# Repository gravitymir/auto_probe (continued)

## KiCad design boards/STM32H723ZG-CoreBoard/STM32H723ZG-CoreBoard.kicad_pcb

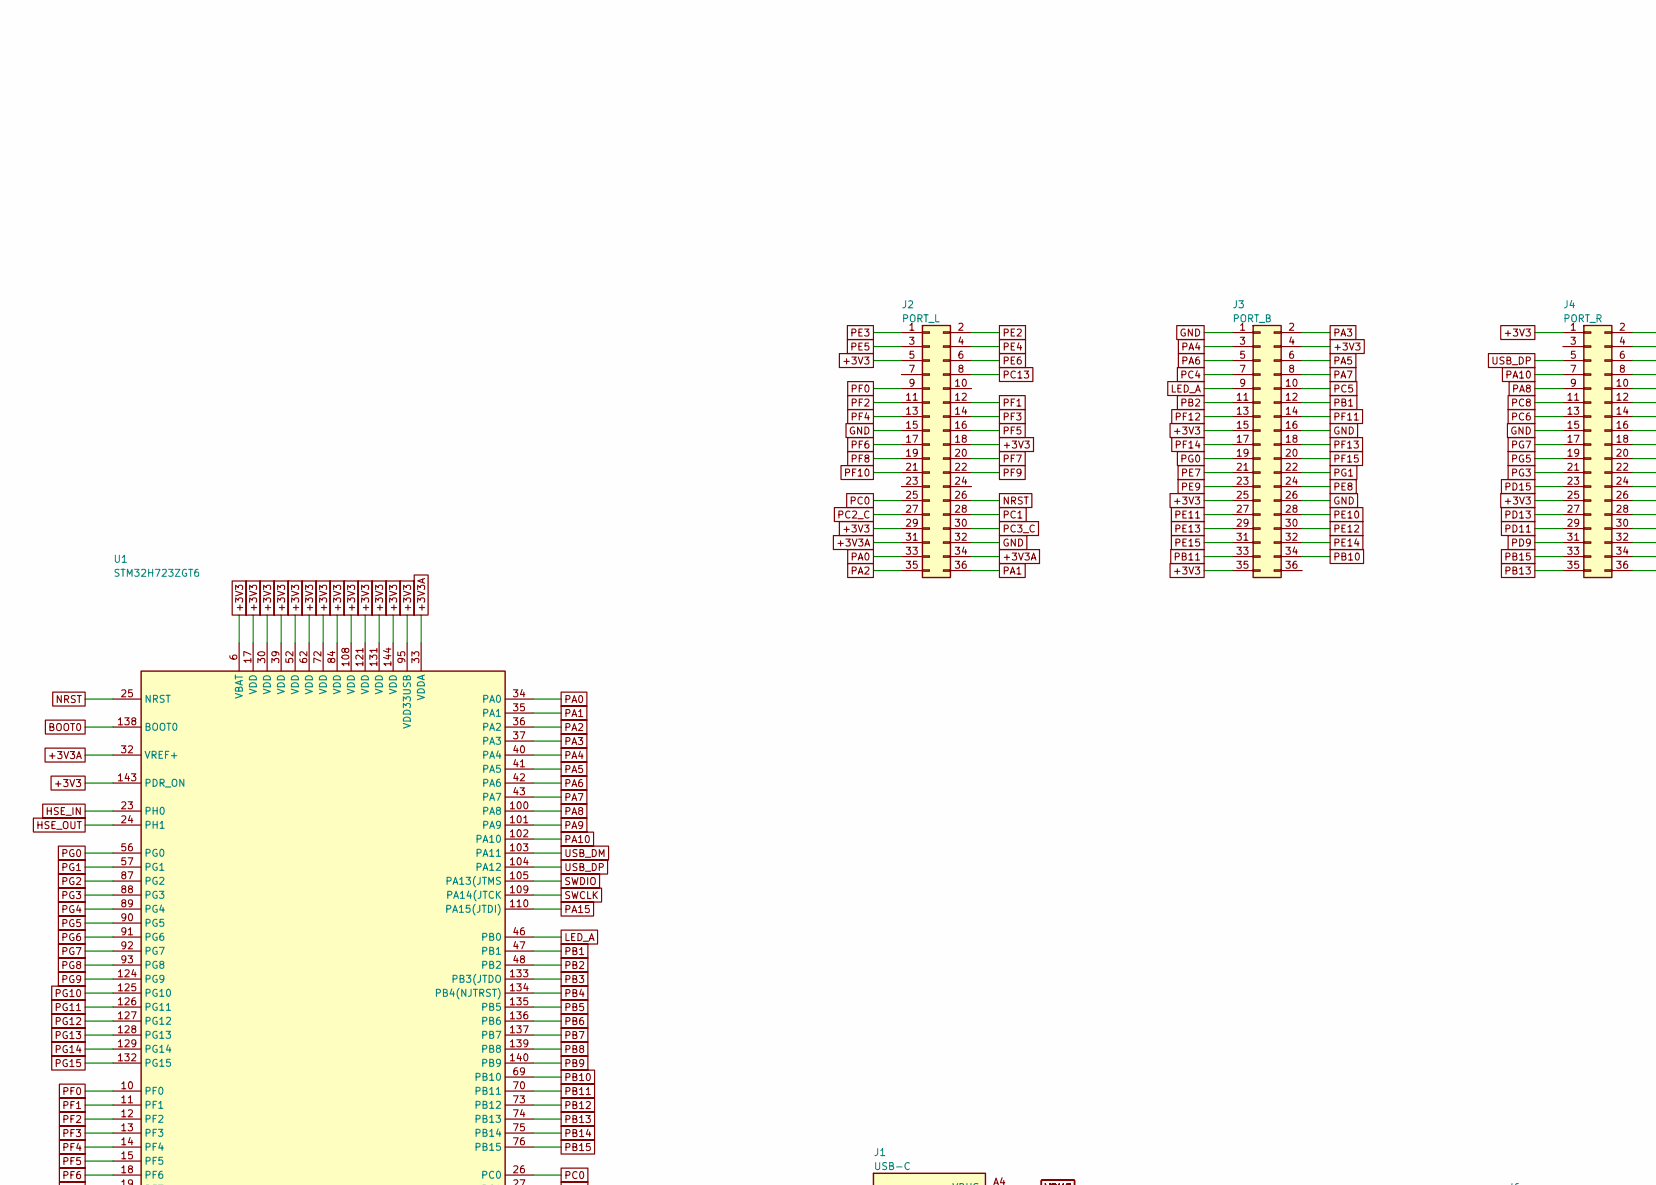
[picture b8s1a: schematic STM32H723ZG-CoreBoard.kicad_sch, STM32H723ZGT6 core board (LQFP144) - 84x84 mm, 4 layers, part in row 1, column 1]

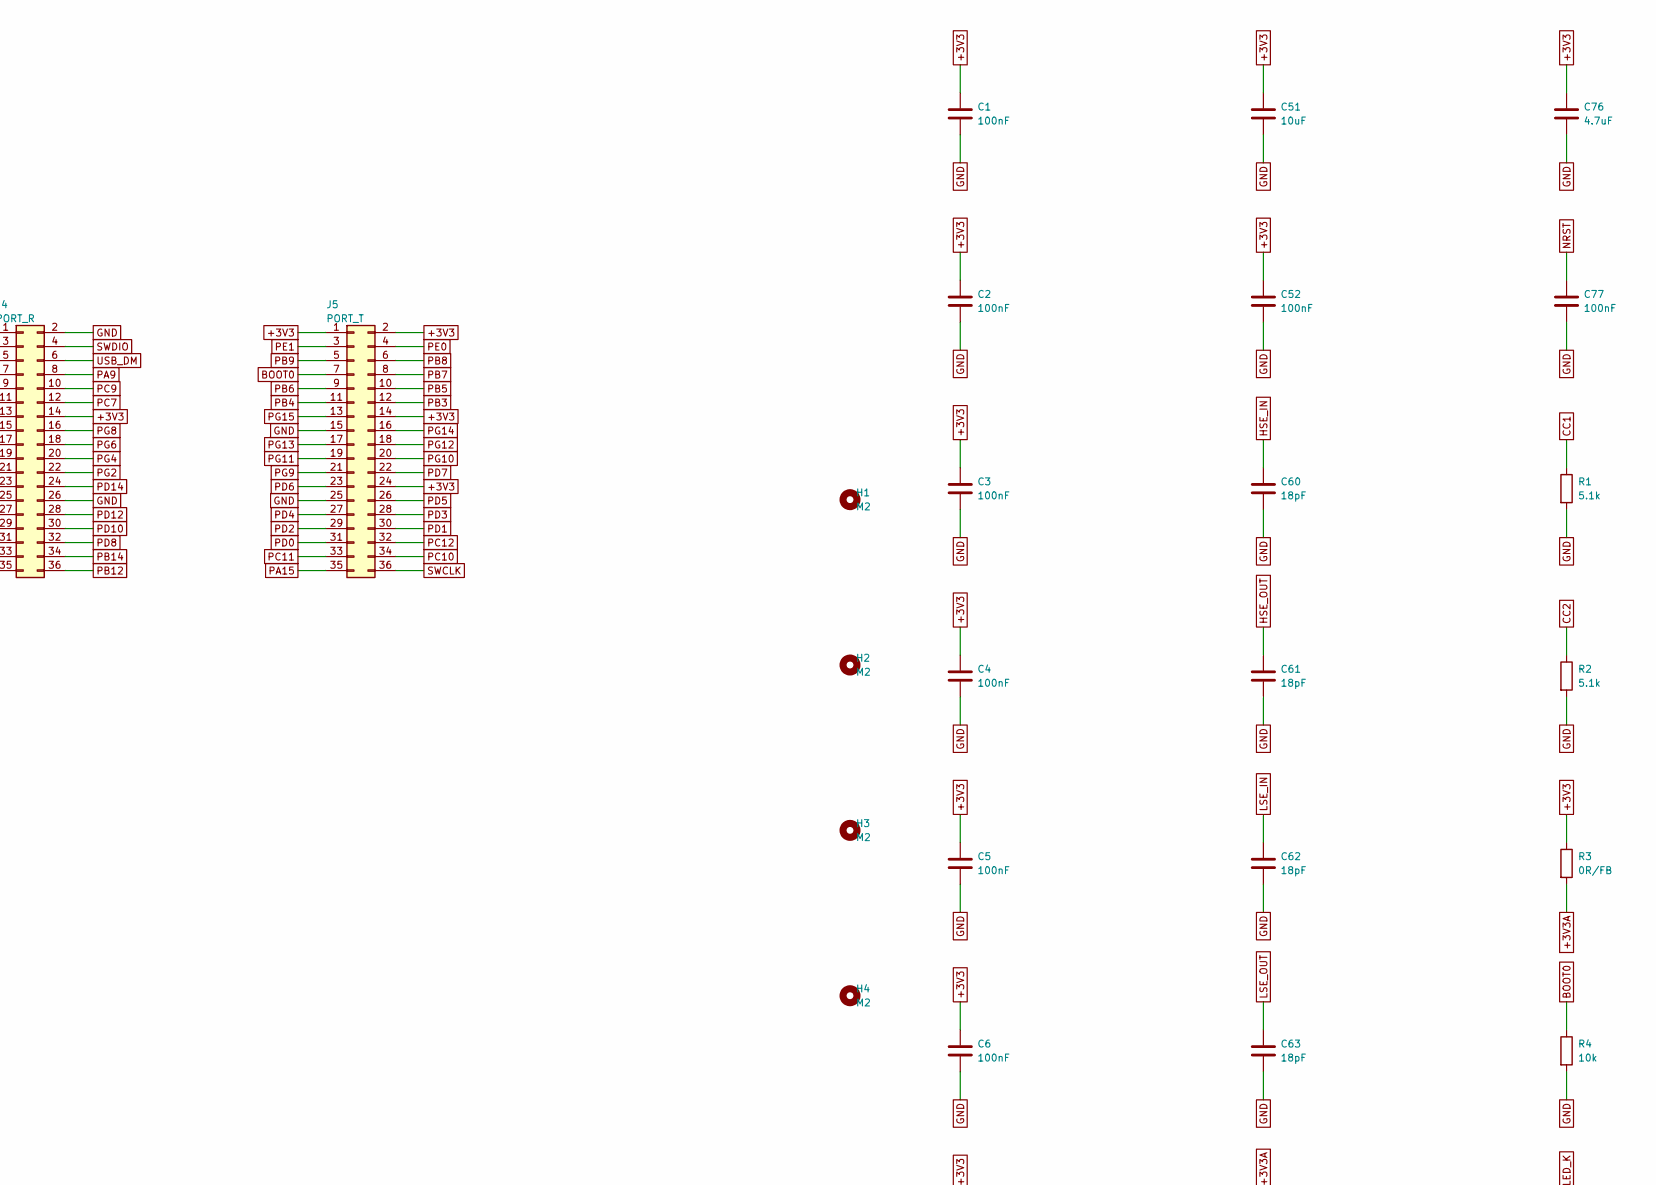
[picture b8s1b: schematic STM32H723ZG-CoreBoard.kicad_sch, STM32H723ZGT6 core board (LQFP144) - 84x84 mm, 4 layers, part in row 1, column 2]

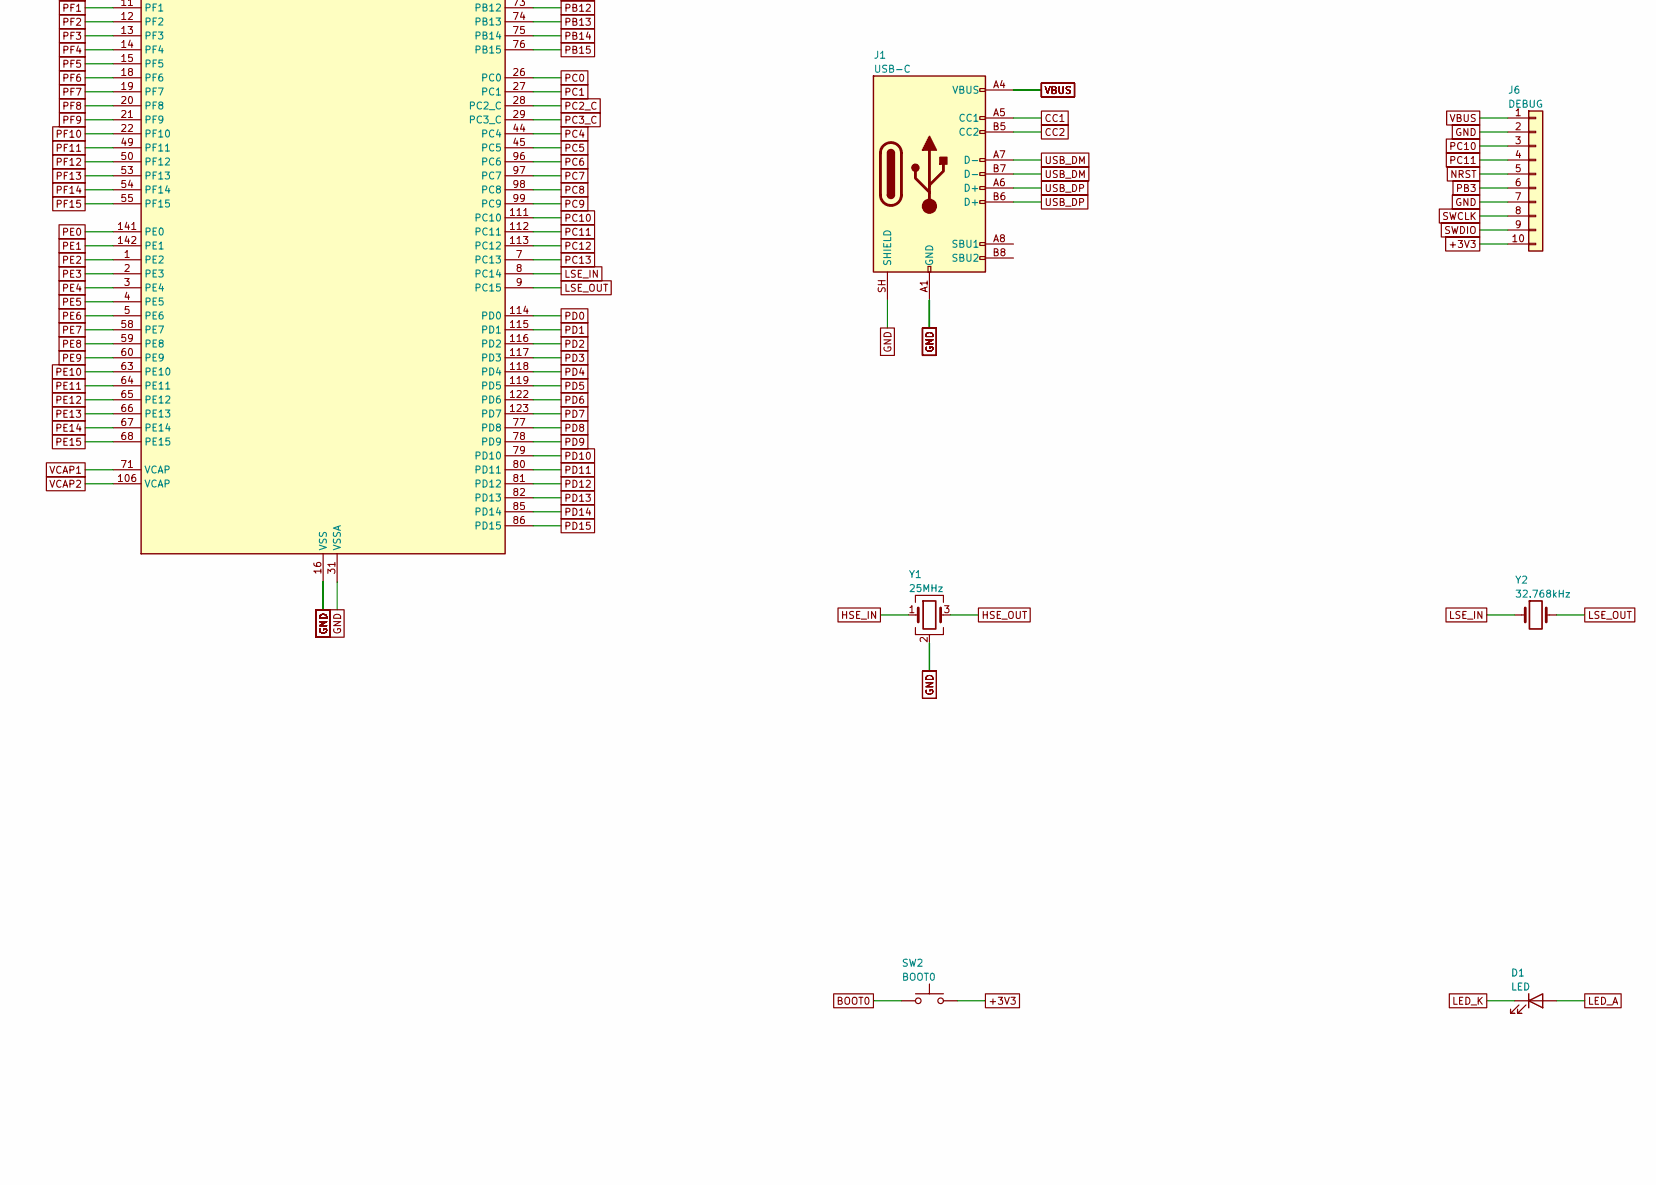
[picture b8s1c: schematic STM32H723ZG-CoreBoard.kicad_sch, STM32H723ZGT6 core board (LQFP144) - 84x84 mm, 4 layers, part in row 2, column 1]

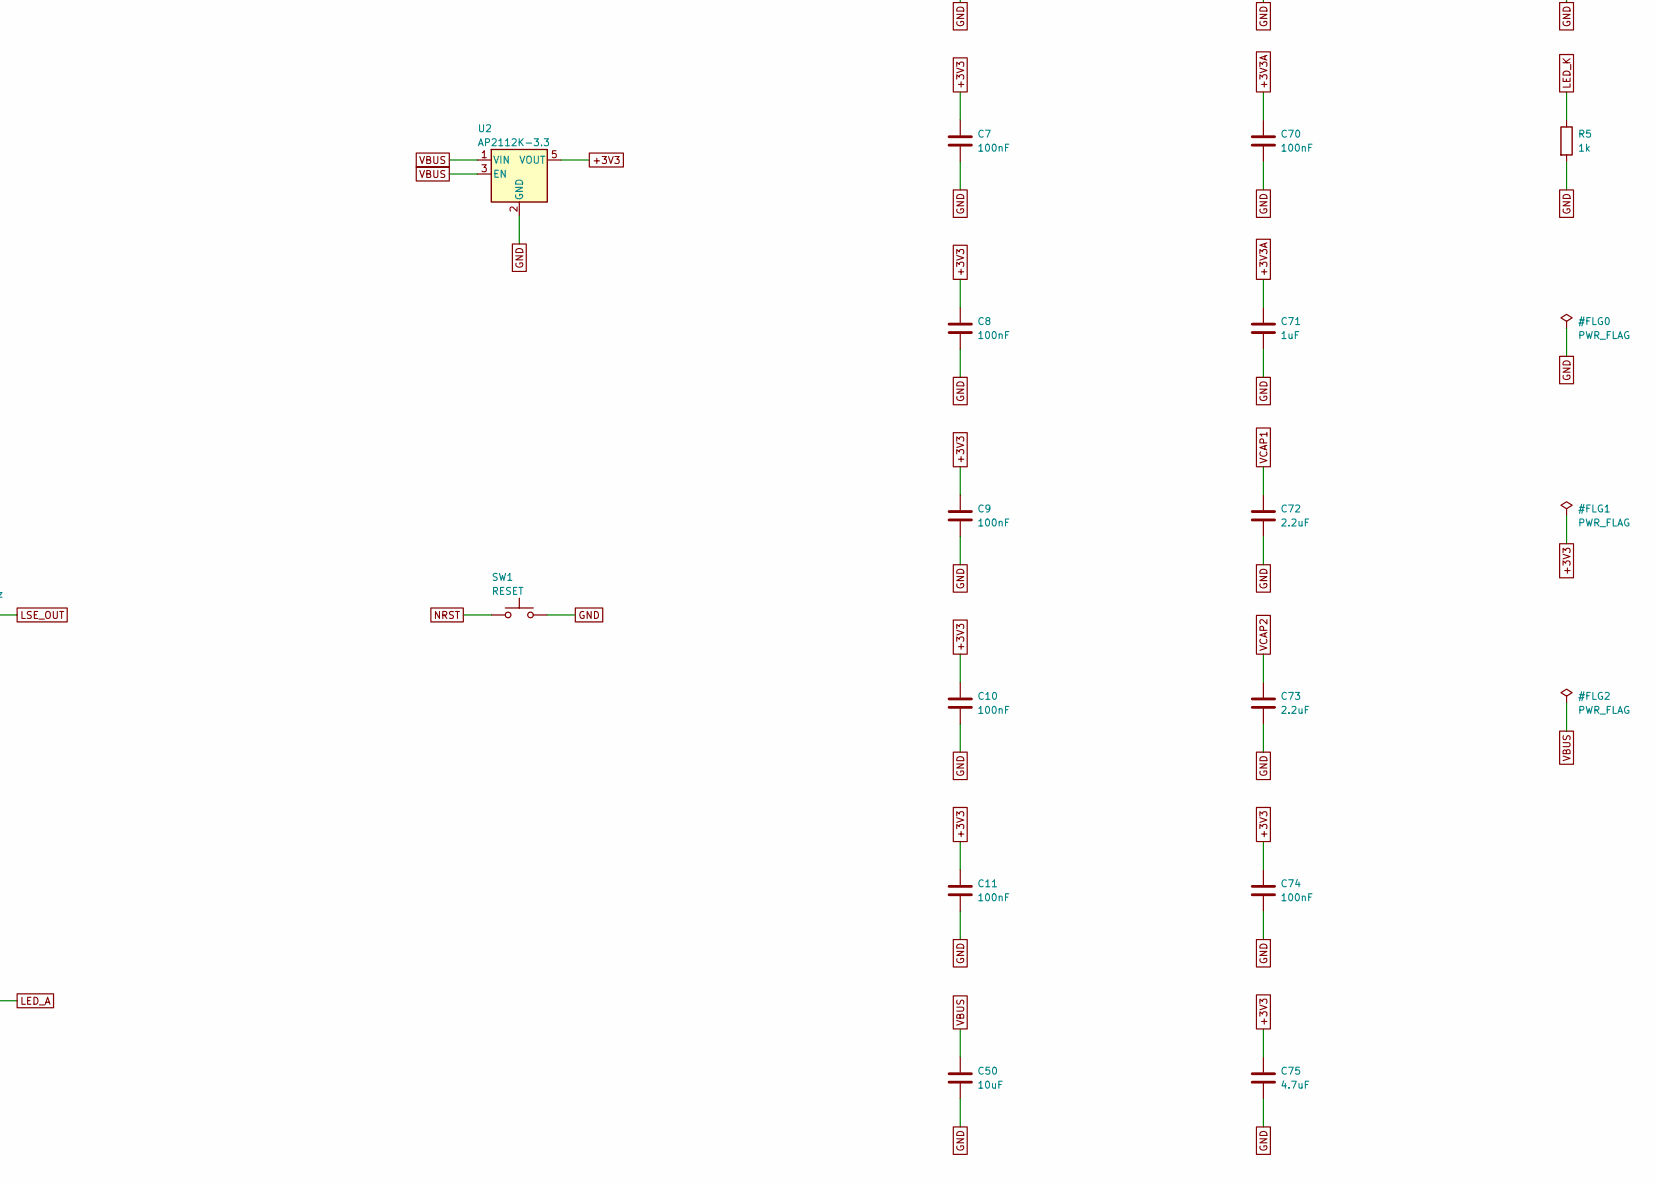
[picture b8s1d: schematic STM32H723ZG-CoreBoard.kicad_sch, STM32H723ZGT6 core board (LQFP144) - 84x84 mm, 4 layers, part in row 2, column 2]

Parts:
C1, C2, C3, C4, C5, C6, C7, C8, C9, C10, C11, C70, C74, C77: 100nF; C_0402_1005Metric
C50, C51: 10uF; C_0805_2012Metric
C52: 100nF; C_0603_1608Metric
C60, C61, C62, C63: 18pF; C_0402_1005Metric
C71: 1uF; C_0603_1608Metric
C72, C73: 2.2uF; C_0603_1608Metric
C75, C76: 4.7uF; C_0805_2012Metric
D1: LED; LED_0805_2012Metric
H1, H2, H3, H4: M2; MountingHole_2.2mm_M2
J1: USB-C; USB_C_Receptacle_HRO_TYPE-C-31-M-12
J2: PORT_L; PinHeader_2x18_P2.54mm_Vertical
J3: PORT_B; PinHeader_2x18_P2.54mm_Vertical
J4: PORT_R; PinHeader_2x18_P2.54mm_Vertical
J5: PORT_T; PinHeader_2x18_P2.54mm_Vertical
J6: DEBUG; PinHeader_1x10_P2.54mm_Vertical
R1, R2: 5.1k; R_0402_1005Metric
R3: 0R/FB; R_0402_1005Metric
R4: 10k; R_0402_1005Metric
R5: 1k; R_0402_1005Metric
SW1: RESET; SW_SPST_SKQG_WithoutStem
SW2: BOOT0; SW_SPST_SKQG_WithoutStem
U1: STM32H723ZGT6; LQFP-144_20x20mm_P0.5mm
U2: AP2112K-3.3; SOT-23-5
Y1: 25MHz; Crystal_SMD_3225-4Pin_3.2x2.5mm
Y2: 32.768kHz; Crystal_SMD_MicroCrystal_CC7V-T1A-2Pin_3.2x1.5mm

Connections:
+3V3: C1.1, C2.1, C3.1, C4.1, C5.1, C6.1, C7.1, C8.1, C9.1, C10.1, C11.1, C51.1, C52.1, C74.1, C75.1, C76.1, J2.5, J2.18, J2.29, J3.4, J3.15, J3.25, J3.35, J4.1, J4.14, J4.25, J5.1, J5.2, J5.14, J5.24, J6.10, R3.1, SW2.2, U1.6 (VBAT), U1.17 (VDD), U1.30 (VDD), U1.39 (VDD), U1.52 (VDD), U1.62 (VDD), U1.72 (VDD), U1.84 (VDD), U1.95 (VDD33USB), U1.108 (VDD), U1.121 (VDD), U1.131 (VDD), U1.143 (PDR_ON), U1.144 (VDD), U2.5 (VOUT)
+3V3A: C70.1, C71.1, J2.31, J2.34, R3.2, U1.32 (VREF+), U1.33 (VDDA)
BOOT0: J5.7, R4.1, SW2.1, U1.138 (BOOT0)
CC1: J1.A5 (CC1), R1.1
CC2: J1.B5 (CC2), R2.1
GND: C1.2, C2.2, C3.2, C4.2, C5.2, C6.2, C7.2, C8.2, C9.2, C10.2, C11.2, C50.2, C51.2, C52.2, C60.2, C61.2, C62.2, C63.2, C70.2, C71.2, C72.2, C73.2, C74.2, C75.2, C76.2, C77.2, J1.A1 (GND), J1.A12 (GND), J1.B1 (GND), J1.B12 (GND), J1.SH (SHIELD), J2.15, J2.32, J3.1, J3.16, J3.26, J4.2, J4.15, J4.26, J5.15, J5.25, J6.2, J6.7, R1.2, R2.2, R4.2, R5.2, SW1.2, U1.16 (VSS), U1.31 (VSSA), U1.38 (VSS), U1.51 (VSS), U1.61 (VSS), U1.83 (VSS), U1.94 (VSS), U1.107 (VSS), U1.120 (VSS), U1.130 (VSS), U2.2 (GND), Y1.2 (G), Y1.4 (G)
HSE_IN: C60.1, U1.23 (PH0), Y1.1
HSE_OUT: C61.1, U1.24 (PH1), Y1.3
LED_A: D1.2 (A), J3.9, U1.46 (PB0)
LED_K: D1.1 (K), R5.1
LSE_IN: C62.1, U1.8 (PC14), Y2.1
LSE_OUT: C63.1, U1.9 (PC15), Y2.2
NRST: C77.1, J2.26, J6.5, SW1.1, U1.25 (NRST)
PA0: J2.33, U1.34 (PA0)
PA1: J2.36, U1.35 (PA1)
PA2: J2.35, U1.36 (PA2)
PA3: J3.2, U1.37 (PA3)
PA4: J3.3, U1.40 (PA4)
PA5: J3.6, U1.41 (PA5)
PA6: J3.5, U1.42 (PA6)
PA7: J3.8, U1.43 (PA7)
PA8: J4.9, U1.100 (PA8)
PA9: J4.8, U1.101 (PA9)
PA10: J4.7, U1.102 (PA10)
PA15: J5.35, U1.110 (PA15(JTDI))
PB1: J3.12, U1.47 (PB1)
PB2: J3.11, U1.48 (PB2)
PB3: J5.12, J6.6, U1.133 (PB3(JTDO)
PB4: J5.11, U1.134 (PB4(NJTRST))
PB5: J5.10, U1.135 (PB5)
PB6: J5.9, U1.136 (PB6)
PB7: J5.8, U1.137 (PB7)
PB8: J5.6, U1.139 (PB8)
PB9: J5.5, U1.140 (PB9)
PB10: J3.34, U1.69 (PB10)
PB11: J3.33, U1.70 (PB11)
PB12: J4.36, U1.73 (PB12)
PB13: J4.35, U1.74 (PB13)
PB14: J4.34, U1.75 (PB14)
PB15: J4.33, U1.76 (PB15)
PC0: J2.25, U1.26 (PC0)
PC1: J2.28, U1.27 (PC1)
PC2_C: J2.27, U1.28 (PC2_C)
PC3_C: J2.30, U1.29 (PC3_C)
PC4: J3.7, U1.44 (PC4)
PC5: J3.10, U1.45 (PC5)
PC6: J4.13, U1.96 (PC6)
PC7: J4.12, U1.97 (PC7)
PC8: J4.11, U1.98 (PC8)
PC9: J4.10, U1.99 (PC9)
PC10: J5.34, J6.3, U1.111 (PC10)
PC11: J5.33, J6.4, U1.112 (PC11)
PC12: J5.32, U1.113 (PC12)
PC13: J2.8, U1.7 (PC13)
PD0: J5.31, U1.114 (PD0)
PD1: J5.30, U1.115 (PD1)
PD2: J5.29, U1.116 (PD2)
PD3: J5.28, U1.117 (PD3)
PD4: J5.27, U1.118 (PD4)
PD5: J5.26, U1.119 (PD5)
PD6: J5.23, U1.122 (PD6)
PD7: J5.22, U1.123 (PD7)
PD8: J4.32, U1.77 (PD8)
PD9: J4.31, U1.78 (PD9)
PD10: J4.30, U1.79 (PD10)
PD11: J4.29, U1.80 (PD11)
PD12: J4.28, U1.81 (PD12)
PD13: J4.27, U1.82 (PD13)
PD14: J4.24, U1.85 (PD14)
PD15: J4.23, U1.86 (PD15)
PE0: J5.4, U1.141 (PE0)
PE1: J5.3, U1.142 (PE1)
PE2: J2.2, U1.1 (PE2)
PE3: J2.1, U1.2 (PE3)
PE4: J2.4, U1.3 (PE4)
PE5: J2.3, U1.4 (PE5)
PE6: J2.6, U1.5 (PE6)
PE7: J3.21, U1.58 (PE7)
PE8: J3.24, U1.59 (PE8)
PE9: J3.23, U1.60 (PE9)
PE10: J3.28, U1.63 (PE10)
PE11: J3.27, U1.64 (PE11)
PE12: J3.30, U1.65 (PE12)
PE13: J3.29, U1.66 (PE13)
PE14: J3.32, U1.67 (PE14)
PE15: J3.31, U1.68 (PE15)
PF0: J2.9, U1.10 (PF0)
PF1: J2.12, U1.11 (PF1)
PF2: J2.11, U1.12 (PF2)
PF3: J2.14, U1.13 (PF3)
PF4: J2.13, U1.14 (PF4)
PF5: J2.16, U1.15 (PF5)
PF6: J2.17, U1.18 (PF6)
PF7: J2.20, U1.19 (PF7)
PF8: J2.19, U1.20 (PF8)
PF9: J2.22, U1.21 (PF9)
PF10: J2.21, U1.22 (PF10)
PF11: J3.14, U1.49 (PF11)
PF12: J3.13, U1.50 (PF12)
PF13: J3.18, U1.53 (PF13)
PF14: J3.17, U1.54 (PF14)
PF15: J3.20, U1.55 (PF15)
PG0: J3.19, U1.56 (PG0)
PG1: J3.22, U1.57 (PG1)
PG2: J4.22, U1.87 (PG2)
PG3: J4.21, U1.88 (PG3)
PG4: J4.20, U1.89 (PG4)
PG5: J4.19, U1.90 (PG5)
PG6: J4.18, U1.91 (PG6)
PG7: J4.17, U1.92 (PG7)
PG8: J4.16, U1.93 (PG8)
PG9: J5.21, U1.124 (PG9)
PG10: J5.20, U1.125 (PG10)
PG11: J5.19, U1.126 (PG11)
PG12: J5.18, U1.127 (PG12)
PG13: J5.17, U1.128 (PG13)
PG14: J5.16, U1.129 (PG14)
PG15: J5.13, U1.132 (PG15)
SWCLK: J5.36, J6.8, U1.109 (PA14(JTCK)
SWDIO: J4.4, J6.9, U1.105 (PA13(JTMS)
USB_DM: J1.A7 (D-), J1.B7 (D-), J4.6, U1.103 (PA11)
USB_DP: J1.A6 (D+), J1.B6 (D+), J4.5, U1.104 (PA12)
VBUS: C50.1, J1.A4 (VBUS), J1.A9 (VBUS), J1.B4 (VBUS), J1.B9 (VBUS), J6.1, U2.1 (VIN), U2.3 (EN)
VCAP1: C72.1, U1.71 (VCAP)
VCAP2: C73.1, U1.106 (VCAP)

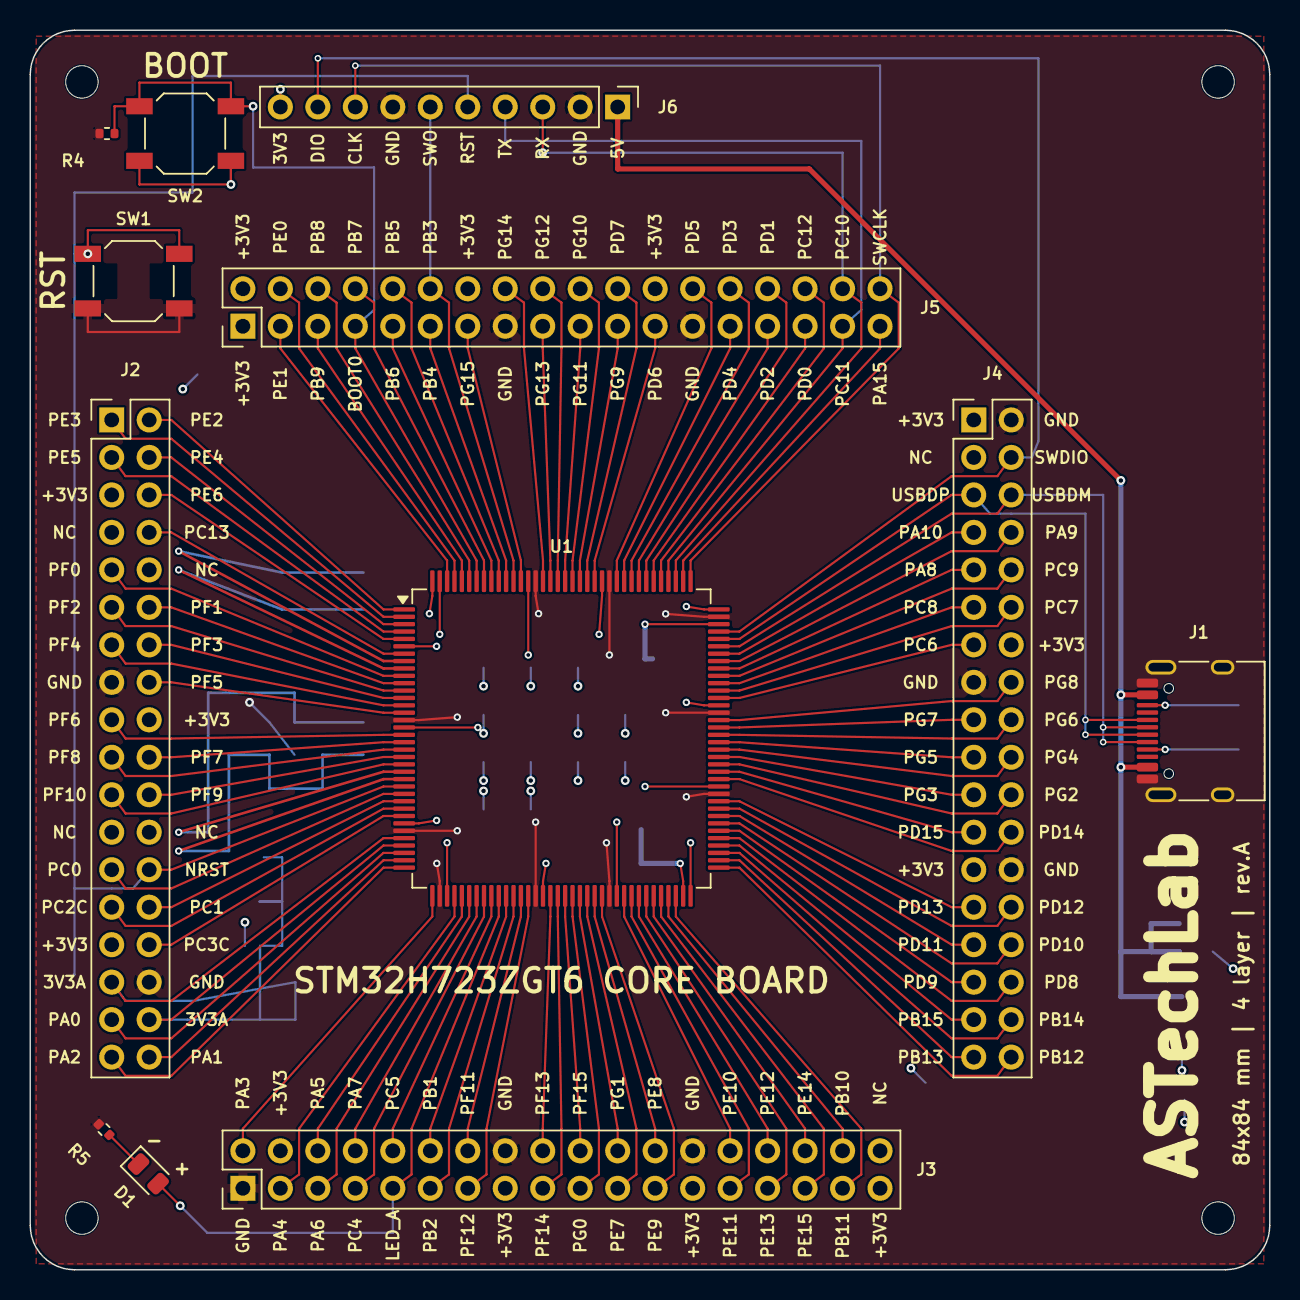
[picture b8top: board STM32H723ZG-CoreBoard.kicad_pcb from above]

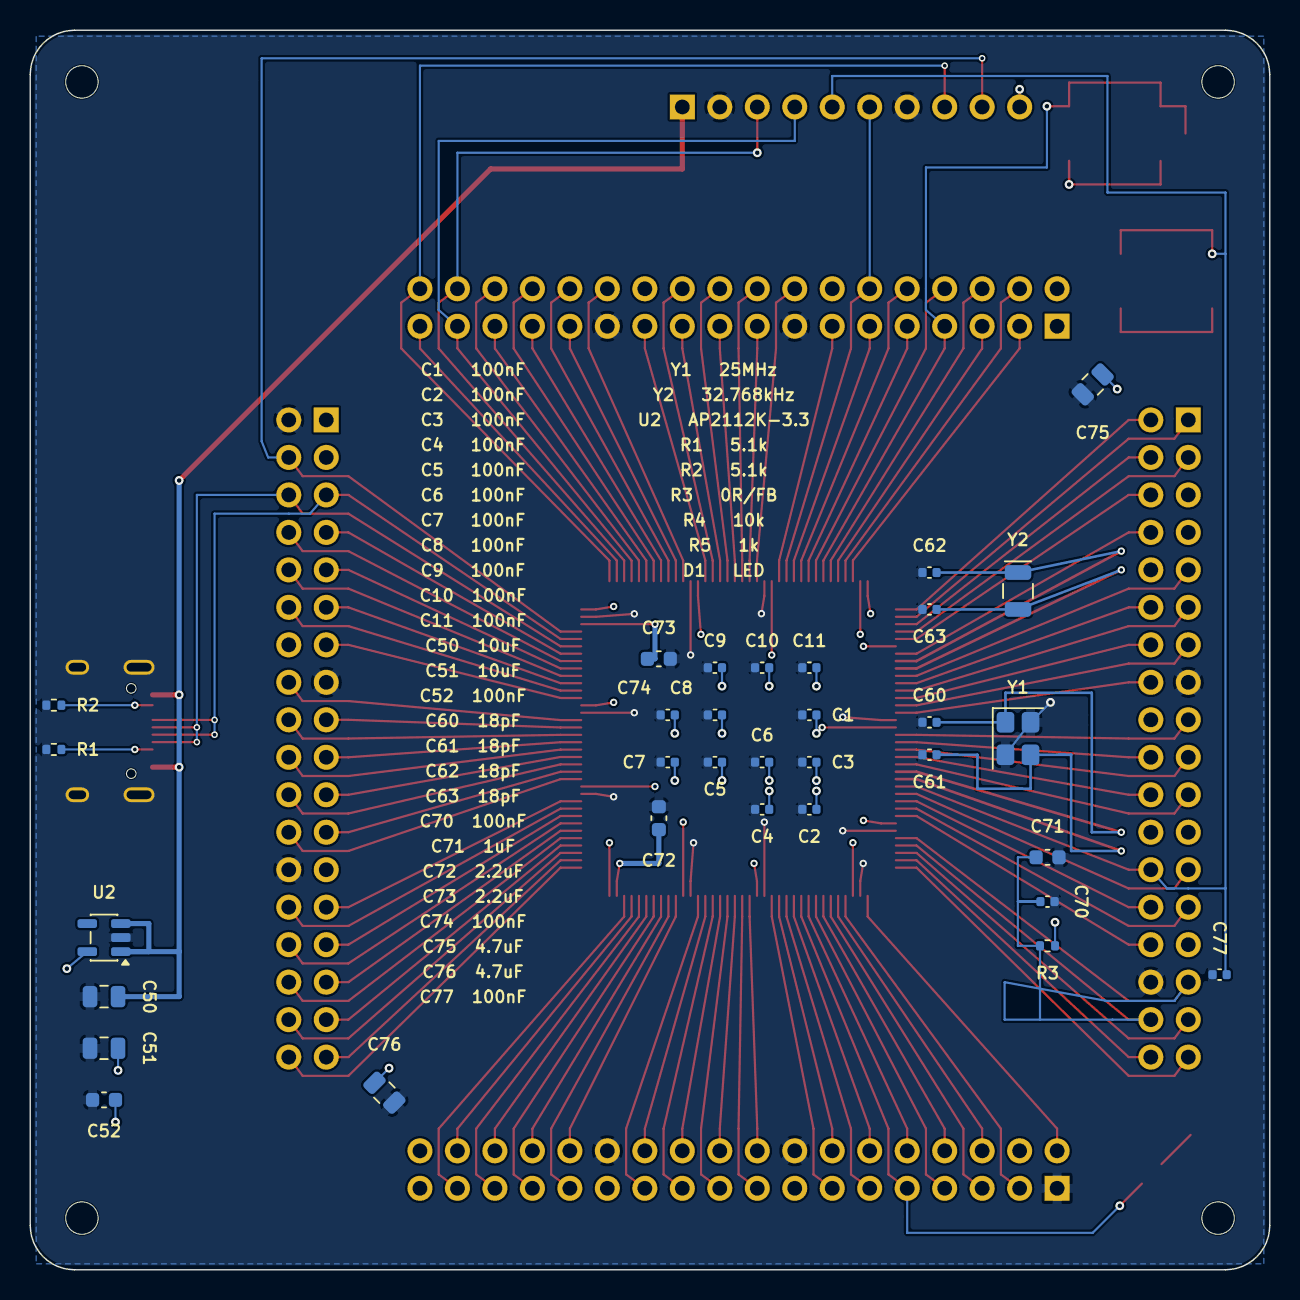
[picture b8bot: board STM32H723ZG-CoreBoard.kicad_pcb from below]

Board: 4 copper layers, 84.0 x 84.0 mm, 48 parts (32 on the bottom side), 125 nets.

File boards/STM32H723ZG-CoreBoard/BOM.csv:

Comment,Designator,Footprint,LCSC Part #,Qty,Note
100nF,"C1,C10,C11,C2,C3,C4,C5,C6,C7,C70,C74,C77,C8,C9",auto_probe:C_0402_1005Metric,C1525,14,проверить наличие на складе
18pF,"C60,C61,C62,C63",auto_probe:C_0402_1005Metric,C1549,4,проверить наличие на складе
100nF,C52,auto_probe:C_0603_1608Metric,C14663,1,проверить наличие на складе
1uF,C71,auto_probe:C_0603_1608Metric,C15849,1,проверить наличие на складе
2.2uF,"C72,C73",auto_probe:C_0603_1608Metric,C23630,2,проверить наличие на складе
10uF,"C50,C51",auto_probe:C_0805_2012Metric,C15850,2,проверить наличие на складе
4.7uF,"C75,C76",auto_probe:C_0805_2012Metric,C1779,2,проверить наличие на складе
25MHz,Y1,auto_probe:Crystal_SMD_3225-4Pin_3.2x2.5mm,C9006,1,проверить наличие на складе; обвязка 18 пФ - только под CL 12...12.5 пФ
32.768kHz,Y2,auto_probe:Crystal_SMD_MicroCrystal_CC7V-T1A-2Pin_3.2x1.5mm,C97606,1,проверить наличие на складе; обвязка 18 пФ - только под CL 12...12.5 пФ
LED,D1,auto_probe:LED_0805_2012Metric,C84256,1,проверить наличие на складе
STM32H723ZGT6,U1,auto_probe:LQFP-144_20x20mm_P0.5mm,C730146,1,проверить наличие на складе
DEBUG,J6,auto_probe:PinHeader_1x10_P2.54mm_Vertical,,1,"выводная: в SMT-монтаж не идёт, паяется отдельно"
PORT_B,J3,auto_probe:PinHeader_2x18_P2.54mm_Vertical,,1,"выводная: в SMT-монтаж не идёт, паяется отдельно"
PORT_L,J2,auto_probe:PinHeader_2x18_P2.54mm_Vertical,,1,"выводная: в SMT-монтаж не идёт, паяется отдельно"
PORT_R,J4,auto_probe:PinHeader_2x18_P2.54mm_Vertical,,1,"выводная: в SMT-монтаж не идёт, паяется отдельно"
PORT_T,J5,auto_probe:PinHeader_2x18_P2.54mm_Vertical,,1,"выводная: в SMT-монтаж не идёт, паяется отдельно"
1k,R5,auto_probe:R_0402_1005Metric,C11702,1,проверить наличие на складе
0R/FB,R3,auto_probe:R_0402_1005Metric,C17168,1,проверить наличие на складе
10k,R4,auto_probe:R_0402_1005Metric,C25744,1,проверить наличие на складе
5.1k,"R1,R2",auto_probe:R_0402_1005Metric,C25905,2,проверить наличие на складе
AP2112K-3.3,U2,auto_probe:SOT-23-5,C51118,1,"проверить наличие на складе; аналог по выводам ME6211C33M5G-N (C82942), SOT-23-5, 1 VIN / 2 GND / 3 EN / 5 VOUT"
BOOT0/RESET,"SW1,SW2",auto_probe:SW_SPST_SKQG_WithoutStem,C318884,2,проверить наличие на складе
USB-C,J1,auto_probe:USB_C_Receptacle_HRO_TYPE-C-31-M-12,C165948,1,проверить наличие на складе

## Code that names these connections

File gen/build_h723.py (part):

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    sides[k].sort(key=lambda n: pads[n][0])
assert all(len(v) == 36 for v in sides.values()), {k: len(v) for k, v in sides.items()}

# Выводы для разъёма прошивки. SWO у H7 только на PB3, а UART берём USART3 (PC10/PC11):
# эта пара выходит на верхнюю гребёнку рядом со SWCLK, тогда как USART1 (PA9/PA10)
# лежит на правой гребёнке за коридором USB, куда дорожку уже не провести.
pin_of = lambda nm: next(n for n in pads if PINNAME[n] == nm)
UTX, URX, SWO = pin_of("PC10"), pin_of("PC11"), pin_of("PB3")

# ---------------------------------------------------------- гребёнки 2x18
HL = 17 * 2.54
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
# Верхнее кольцо, слева направо: светодиод, RST, BOOT, разъём прошивки - как на G474
TOPY = Y0 + 7.0
# Светодиод - в нижнем левом углу, у своей же гребёнки: вывод PB0 выходит на J3,
# и из верхнего ряда до него шла дорожка в 126 мм через всё левое кольцо.
# Пара стоит по диагонали в свободном углу между крепёжным отверстием, J2 и J3;
# анод D1 смотрит на северо-восток, в сторону своей гребёнки.
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JY = Y0 + 5.2                              # ряд разъёма прошивки: подписи ушли под
                                           # него, сверху остались только полосы SWO/NRST
# Разъём развёрнут: 5V у восточного края, ближе к USB. Положение задано так, чтобы
# контакт SWO встал ровно над своим падом на J5 - тогда отвод к PB3 идёт по прямой.
JX = hdrof[SWO]["x"] + 5 * 2.54             # контакт 1 - восточный край разъёма
b.place("J6", HDRLIB, "PinHeader_1x10_P2.54mm_Vertical", JX, JY, 270, value="DEBUG")
b.place("U2", "Package_TO_SOT_SMD", "SOT-23-5", X1 - 5.0, UCY + 14.0, 0, back=True, value="AP2112K-3.3")
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# В кольце между гребёнкой и краем платы на шелк остаётся 3.7 мм - пятизначное
# имя шрифтом 0.8 мм туда уже не входит. Для таких на шелке короткая форма;
# в цепях, схеме и PINOUT.csv имена остаются полными.
SILKNAME = {"+3V3A": "3V3A", "PC2_C": "PC2C", "PC3_C": "PC3C",
            "USB_DP": "USBDP", "USB_DM": "USBDM"}
lbl_txt = lambda mn: "NC" if mn in NO_HEADER else SILKNAME.get(mcu_net(mn), mcu_net(mn))
# Внутренние строки отодвинуты так, чтобы шрифт 0.8 мм не задевал контур
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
